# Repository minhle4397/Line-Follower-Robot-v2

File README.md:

Making Hardware compact
Schematic

Layout 

3D image

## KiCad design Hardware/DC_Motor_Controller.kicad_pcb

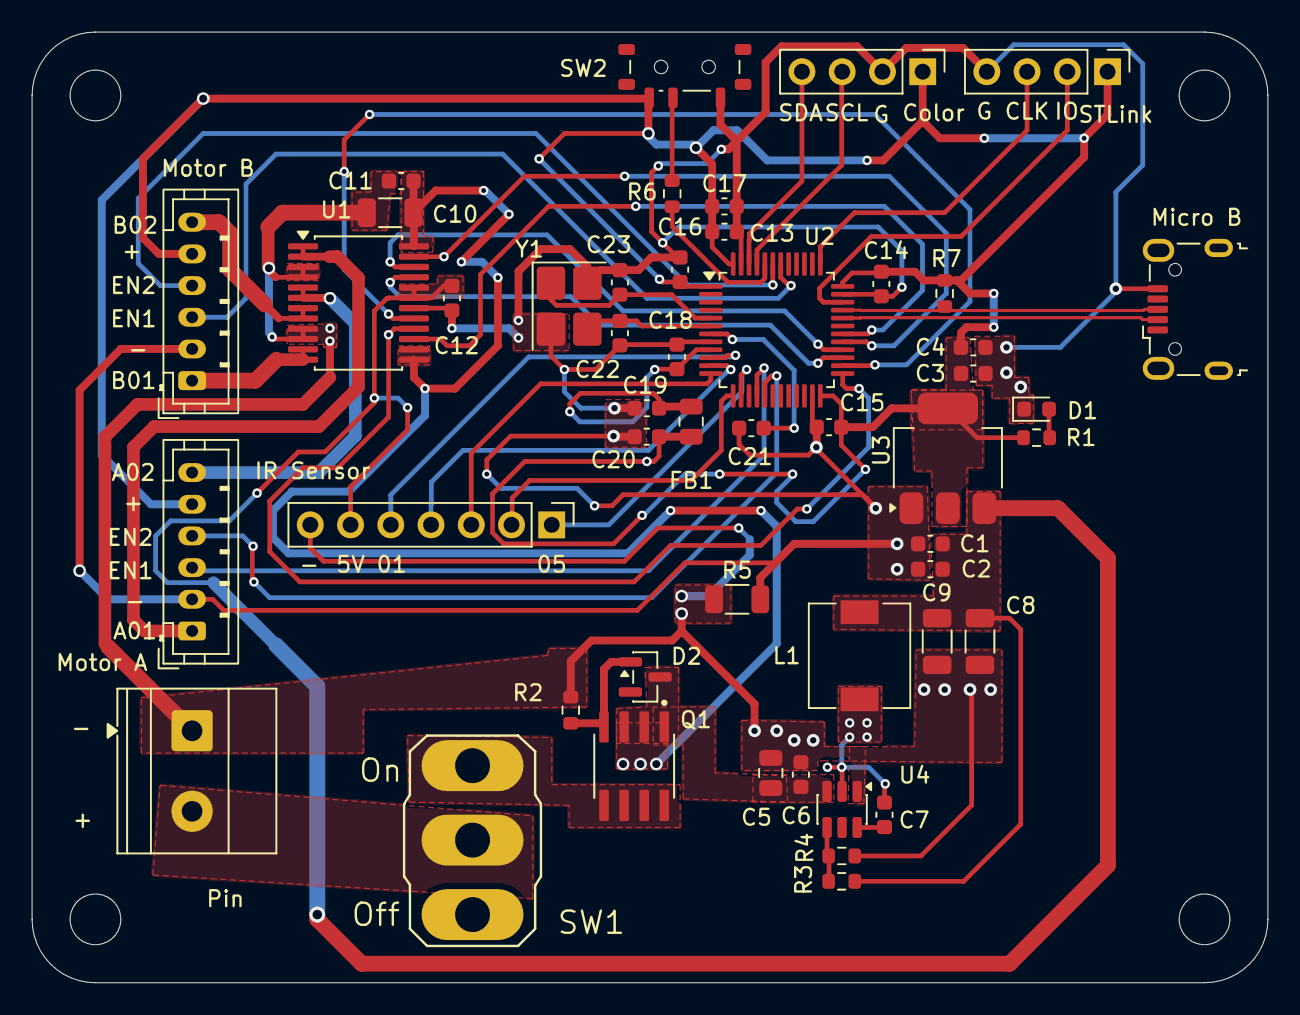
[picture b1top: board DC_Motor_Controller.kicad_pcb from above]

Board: 2 copper layers, 78.0 x 60.0 mm, 53 parts (0 on the bottom side), 43 nets.

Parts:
C1, C3: 10uF 0603/10V; C_0603_1608Metric
C2, C4, C6, C7, C13, C14, C15, C16, C21: 100nF 0603; C_0603_1608Metric
C5: 10uF 0805/25V; C_0805_2012Metric
C8, C9: 22uF/25v; C_1206_3216Metric
C10: 10uF 1206/Tantalum 25V; C_1206_3216Metric
C11, C12: 100nF 0603/50V; C_0603_1608Metric
C17: 10uF 0603; C_0603_1608Metric
C18: 10nF 0603; C_0603_1608Metric
C19, C20: 1uF 0603; C_0603_1608Metric
C22, C23: 10pF 0603; C_0603_1608Metric
Color : Color Sensors; PinHeader_1x04_P2.54mm_Vertical
D1: LED_Green; LED_0603_1608Metric
D2: BZX84C12; SOT-23
FB1: 120R 0805; C_0805_2012Metric
H1, H2, H3, H4: MountingHole; MountingHole_3.2mm_M3
IR Sensor: IR Sensors; PinHeader_1x07_P2.54mm_Vertical
L1: 15uH; L_6.3x6.3_H3
Micro B: USB_B_Micro; USB_Micro-B_Wuerth_629105150521
Motor A: MotorA; JST_PH_B6B-PH-K_1x06_P2.00mm_Vertical
Motor B: MotorB; JST_PH_B6B-PH-K_1x06_P2.00mm_Vertical
Pin: Domino 1x2; TerminalBlock_Phoenix_MKDS-1,5-2-5.08_1x02_P5.08mm_Horizont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
Q1: AO4407A; SOIC127P600X175-8N
R1: 4.7k/0603; R_0603_1608Metric
R2, R3: 100k/0603; R_0603_1608Metric
R4: 13.3k/0603; R_0603_1608Metric
R5: 0R 1206; R_1206_3216Metric
R6: 10k 0603; R_0603_1608Metric
R7: 1k5 0603; R_0603_1608Metric
STLink: ST-LINK; PinHeader_1x04_P2.54mm_Vertical
SW1: MTS_102; MTS-102
SW2: MSK-12C02; SW_SPDT_Shouhan_MSK12C02
U1: TB6612FNG; SSOP-24_5.3x8.2mm_P0.65mm
U2: STM32F103C8T6; LQFP-48_7x7mm_P0.5mm
U3: AMS1117-3.3; SOT-223-3_TabPin2
U4: TPS54202DDC; SOT-23-6
Y1: 16MHz; Crystal_SMD_3225-4Pin_3.2x2.5mm_HandSoldering

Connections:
3.3V: C3.1, C4.1, C13.1, C14.1, C15.1, C16.1, C17.1, C20.1, Color.1, FB1.2, Motor A.5, Motor B.5, R1.1, R7.2, STLink.1, SW2.3 (C), U2.1 (VBAT), U2.24 (VDD), U2.36 (VDD), U2.48 (VDD), U3.2 (VO)
5V: C1.1, C2.1, C8.1, C9.1, C12.1, IR Sensor.6, L1.2, R3.1, U1.19 (STBY), U1.20 (VCC), U3.3 (VI)
+3.3VA: C18.1, C19.1, FB1.1, U2.9 (VDDA)
/MCU/BOOT0: R6.2, U2.44 (BOOT0)
/MCU/HSE_In: C23.1, U2.5 (PD0), Y1.1
/MCU/HSE_Out: C22.1, U2.6 (PD1), Y1.3
/MCU/NRST: C21.1, U2.7 (NRST)
/MCU/SWCLK: STLink.3, U2.37 (PA14)
/MCU/SWDIO: STLink.2, U2.34 (PA13)
/MCU/SW_BOOT0: R6.1, SW2.2 (B)
/MCU/USB_D+: Micro B.3 (D+), R7.1, U2.33 (PA12)
/MCU/USB_D-: Micro B.2 (D-), U2.32 (PA11)
A02: Motor A.6, U1.5 (AO2), U1.6 (AO2)
AIN1: U1.21 (AIN1), U2.27 (PB14)
AIN2: U1.22 (AIN2), U2.28 (PB15)
AO1: Motor A.1, U1.1 (AO1), U1.2 (AO1)
BIN1: U1.17 (BIN1), U2.26 (PB13)
BIN2: U1.16 (BIN2), U2.25 (PB12)
BO1: Motor B.1, U1.11 (BO1), U1.12 (BO1)
BO2: Motor B.6, U1.7 (BO2), U1.8 (BO2)
ENA_1: Motor A.3, U2.16 (PA6)
ENA_2: Motor A.4, U2.17 (PA7)
ENB_1: Motor B.3, U2.42 (PB6)
ENB_2: Motor B.4, U2.43 (PB7)
GND: C1.2, C2.2, C3.2, C4.2, C12.2, C13.2, C14.2, C15.2, C16.2, C17.2, C18.2, C19.2, C20.2, C21.2, C22.2, C23.2, Color.2, D1.1 (K), Micro B.5 (GND), Motor A.2, Motor B.2, R5.2, STLink.4, SW2.1 (A), U1.18 (GND), U2.8 (VSSA), U2.23 (VSS), U2.35 (VSS), U2.47 (VSS), U3.1 (GND), Y1.2 (G), Y1.4 (G)
GNDPWR: C5.2, C6.2, C8.2, C9.2, C10.2, C11.2, IR Sensor.7, Pin.1, R2.1, R4.2, R5.1, U1.3 (PGND1), U1.4 (PGND1), U1.9 (PGND2), U1.10 (PGND2), U4.1 (GND)
unnamed: D1.2 (A), R1.2
unnamed: D2.1 (A), Q1.4, R2.2
unnamed: Pin.2, SW1.2 (B)
unnamed: Q1.5, Q1.6, Q1.7, Q1.8, SW1.1 (A)
unnamed: C7.1, U4.6 (BOOT)
unnamed: R3.2, R4.1, U4.4 (FB)
unnamed: C7.2, L1.1, U4.2 (SW)
O1: IR Sensor.5, U2.10 (PA0)
O2: IR Sensor.4, U2.11 (PA1)
O3: IR Sensor.3, U2.12 (PA2)
O4: IR Sensor.2, U2.13 (PA3)
O5: IR Sensor.1, U2.14 (PA4)
PWMA: U1.23 (PWMA), U2.29 (PA8)
PWMB: U1.15 (PWMB), U2.30 (PA9)
SCL: Color.3, U2.45 (PB8)
SDA: Color.4, U2.46 (PB9)
input: C5.1, C6.1, C10.1, C11.1, D2.3 (K), Q1.1, Q1.2, Q1.3, U1.13 (VM2), U1.14 (VM3), U1.24 (VM1), U4.3 (VIN)
